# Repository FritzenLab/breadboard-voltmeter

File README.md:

# breadboard-voltmeter
 a voltmeter with OLED display on a breadboard, using CH32V003

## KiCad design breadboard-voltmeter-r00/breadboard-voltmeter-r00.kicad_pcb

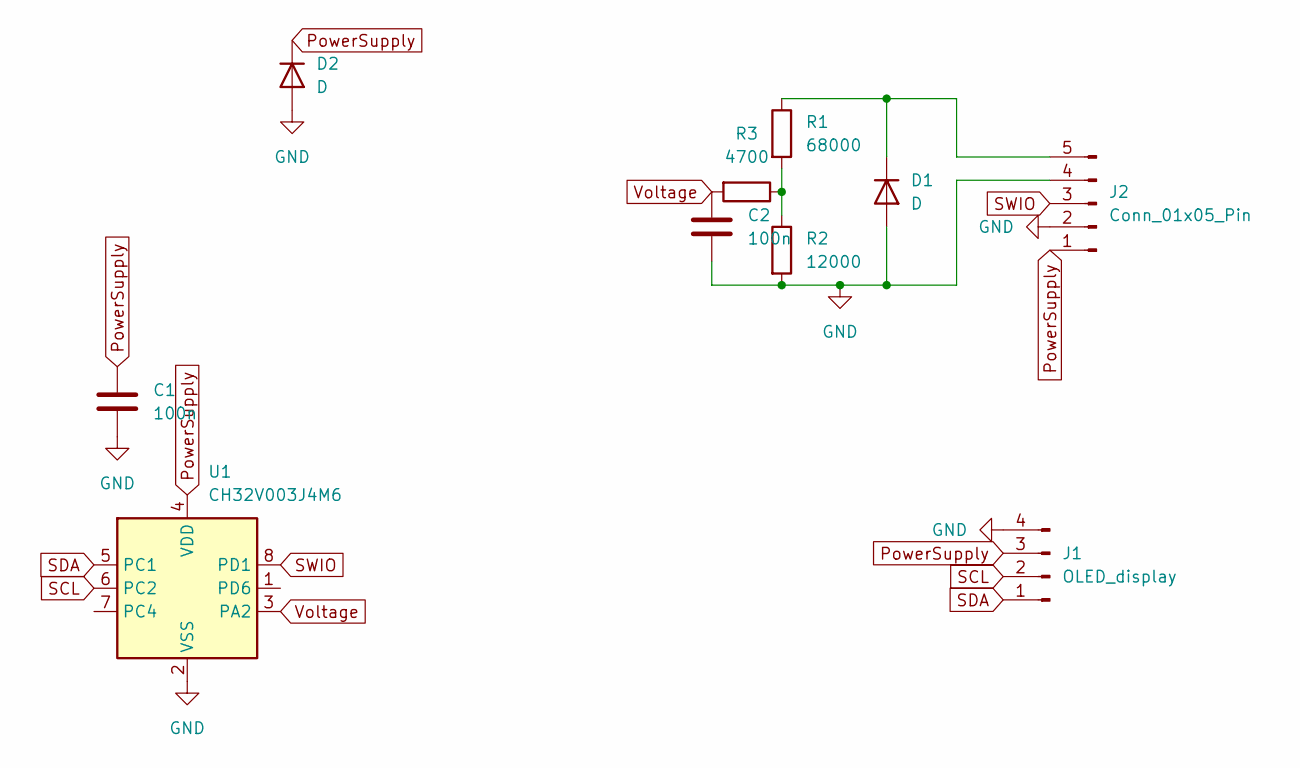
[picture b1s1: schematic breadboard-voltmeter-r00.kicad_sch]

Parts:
C1, C2: 100n; C_0805_2012Metric
D1, D2: D; D_MiniMELF
J1: OLED_display; PinHeader_1x04_P2.54mm_Vertical
J2: Conn_01x05_Pin; PinHeader_1x05_P2.54mm_Vertical
R1: 68000; R_0805_2012Metric
R2: 12000; R_0805_2012Metric
R3: 4700; R_0805_2012Metric
U1: CH32V003J4M6; SO-8_3.9x4.9mm_P1.27mm

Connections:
GND: C1.2, C2.2, D1.2 (A), D2.2 (A), J1.4, J2.2, J2.4, R2.2, U1.2 (VSS)
unnamed: D1.1 (K), J2.5, R1.1
unnamed: R1.2, R2.1, R3.1
PowerSupply: C1.1, D2.1 (K), J1.3, J2.1, U1.4 (VDD)
SCL: J1.2, U1.6 (PC2)
SDA: J1.1, U1.5 (PC1)
SWIO: J2.3, U1.8 (PD1)
Voltage: C2.1, R3.2, U1.3 (PA2)

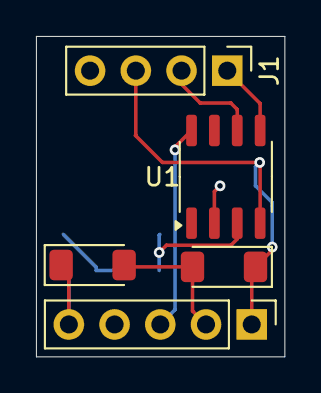
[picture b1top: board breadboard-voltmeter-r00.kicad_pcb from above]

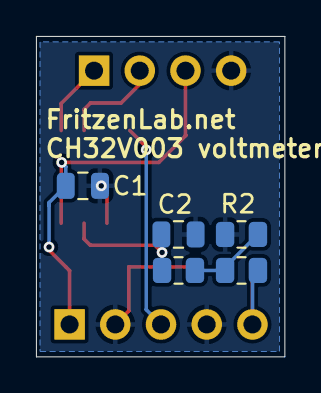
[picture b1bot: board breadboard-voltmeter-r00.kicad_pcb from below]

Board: 2 copper layers, 13.8 x 17.8 mm, 10 parts (5 on the bottom side), 8 nets.

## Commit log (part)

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2025-01-31 added Kicad schematics
2025-01-31 started schematics
2025-01-31 created PCB
2025-02-01 finished design, ready to production
2025-02-01 backups
2025-02-21 updated resistive divider values
2025-02-22 edited schematics
